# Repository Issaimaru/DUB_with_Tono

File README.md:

# DUB_with_Tono
[DriveUnit_Bseries](https://github.com/Issaimaru/MoterDriver_v1)を遠野に刺せるように変換する基板

## 基板外形図<br>
**表**

**裏**

<br>

**実際にDUBと繋げるとこんな感じ**<br>
<br>
~~ちょっと見栄え悪いですね...~~

## 値段<br>
部品を使用していないため，基板代のみ．

## 注意事項
1. この基板を使うと定格電流が野獣と同じくらいになるため，極端に大きい出力が必要な場合には使用しないでください．
1. DUBとはんだ付けをする際は，基板裏面の三角の印が合う向きではんだ付けを行うようにしてください．
1. 逆接すると短絡し大電流が流れます．IN，THRUの矢印の向きに遠野のIN，THRUがあるように接続してください．
1. DUB側で，線で囲まれている部分は電気的に繋げて大丈夫です．はんだ付けする際は取れにくくするために繋げてください．
1. シルクの精度が悪く，裏面のQRコードは読み込めません．

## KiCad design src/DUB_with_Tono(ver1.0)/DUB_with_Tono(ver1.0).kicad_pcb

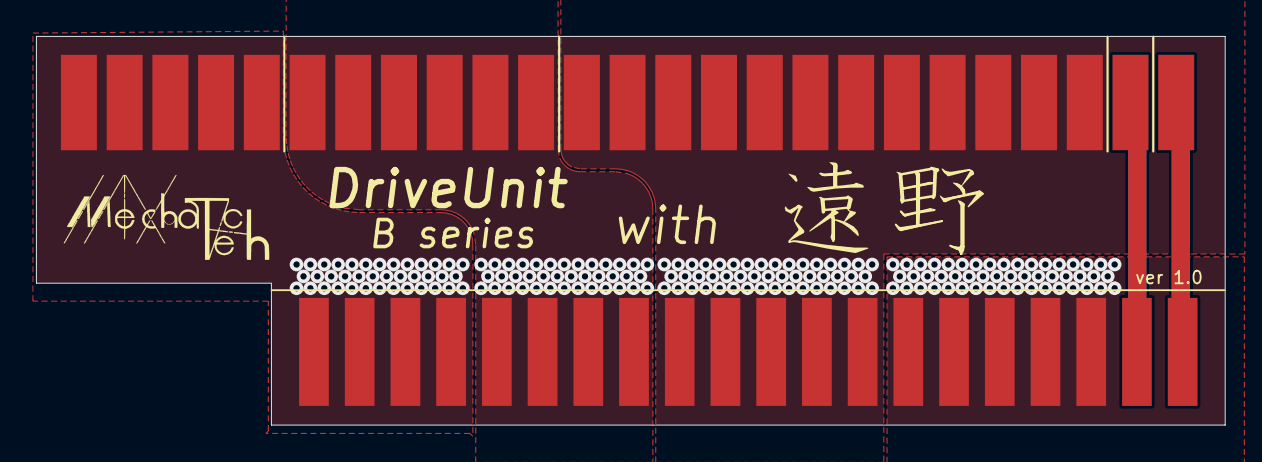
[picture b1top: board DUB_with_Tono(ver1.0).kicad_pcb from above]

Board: 2 copper layers, 66.0 x 21.6 mm, 3 parts (0 on the bottom side), 8 nets.

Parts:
DUB1: 10046971-019LF
U$1: YAJU; TOONO
遠野1: 5-5530843-4

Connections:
/DIR_IN: DUB1.P$26, 遠野1.P$21
/GND_IN: DUB1.P$24, 遠野1.P$19
/PWM_IN: DUB1.P$25, 遠野1.P$20
/SA: DUB1.P$1, DUB1.P$2, DUB1.P$3, DUB1.P$4, DUB1.P$5, DUB1.P$45, DUB1.P$46, DUB1.P$47, DUB1.P$48, DUB1.P$49, DUB1.P$50, 遠野1.P$1, 遠野1.P$2, 遠野1.P$3, 遠野1.P$4, 遠野1.P$37, 遠野1.P$38, 遠野1.P$39, 遠野1.P$40
/SB: DUB1.P$6, DUB1.P$7, DUB1.P$8, DUB1.P$9, DUB1.P$10, DUB1.P$11, DUB1.P$40, DUB1.P$41, DUB1.P$42, DUB1.P$43, DUB1.P$44, 遠野1.P$5, 遠野1.P$6, 遠野1.P$7, 遠野1.P$8, 遠野1.P$33, 遠野1.P$34, 遠野1.P$35, 遠野1.P$36
/VCC_IN: DUB1.P$27, 遠野1.P$22
GND: DUB1.P$28, DUB1.P$29, DUB1.P$30, DUB1.P$31, DUB1.P$32, DUB1.P$33, DUB1.P$34, DUB1.P$35, DUB1.P$36, DUB1.P$37, DUB1.P$38, DUB1.P$39, 遠野1.P$14, 遠野1.P$15, 遠野1.P$16, 遠野1.P$17, 遠野1.P$18, 遠野1.P$23, 遠野1.P$24, 遠野1.P$25, 遠野1.P$26, 遠野1.P$27
VCC: DUB1.P$12, DUB1.P$13, DUB1.P$14, DUB1.P$15, DUB1.P$16, DUB1.P$17, DUB1.P$18, DUB1.P$19, DUB1.P$20, DUB1.P$21, DUB1.P$22, DUB1.P$23, 遠野1.P$9, 遠野1.P$10, 遠野1.P$11, 遠野1.P$12, 遠野1.P$13, 遠野1.P$28, 遠野1.P$29, 遠野1.P$30, 遠野1.P$31, 遠野1.P$32

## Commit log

2022-06-27 キャッシュの削除
2022-06-28 ベタの追加
2022-06-28 ビアの追加
2022-06-28 前バージョン
2022-06-29 Eagle移行前_基板配線完成
2022-06-29 Eagle移行前_遠野ライブラリの修正
2022-06-29 デザインの完成
2022-06-29 gerberの追加
2022-06-29 はんだ補助の線の追加
2022-06-29 Update README.md
    基板外形図の追加
2022-06-30 Update README.md
    誤字の訂正
2022-08-06 Update LICENSE
